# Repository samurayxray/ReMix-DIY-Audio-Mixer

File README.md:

# ReMix. DIY Audio Mixer

I want to build a desktop mixer for my PC using parts recovered from an old AMPRO mixer where possible.

## My idea

The planned design includes four faders, buttons, 6.35 mm audio jacks and a 3D-printed enclosure. I want mixer handle audio and control application volumes on my PC. These functions will need circuits and software.

## progress

I have opened old mixer removed a four‑channel board and photographed both sides. Board contains faders, rotary potentiometers, buttons, LEDs, XLR sockets and jack sockets. Two capacitors failed in mixer. I am keeping power supply out of this project. Recovered components have not been tested yet. I also have not confirmed fader resistance values or pin connections.

## Circuit and enclosure

I plan to use KiCad for schematic and PCB and AutoCAD for enclosure. Enclosure dimensions and mounting holes will depend on components actually used.

## Next steps

- Identify and test one fader.

- Check buttons and audio sockets.

- Decide how audio circuit and USB controls will work.

- Draw schematic and prepare parts list.

- Measure components before designing enclosure.

## Status

Project is still, in planning and component‑checking stage. No working prototype yet.

made by sx1

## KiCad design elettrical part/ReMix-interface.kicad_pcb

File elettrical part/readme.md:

I’m tired of writing README files for electronic circuit boards.

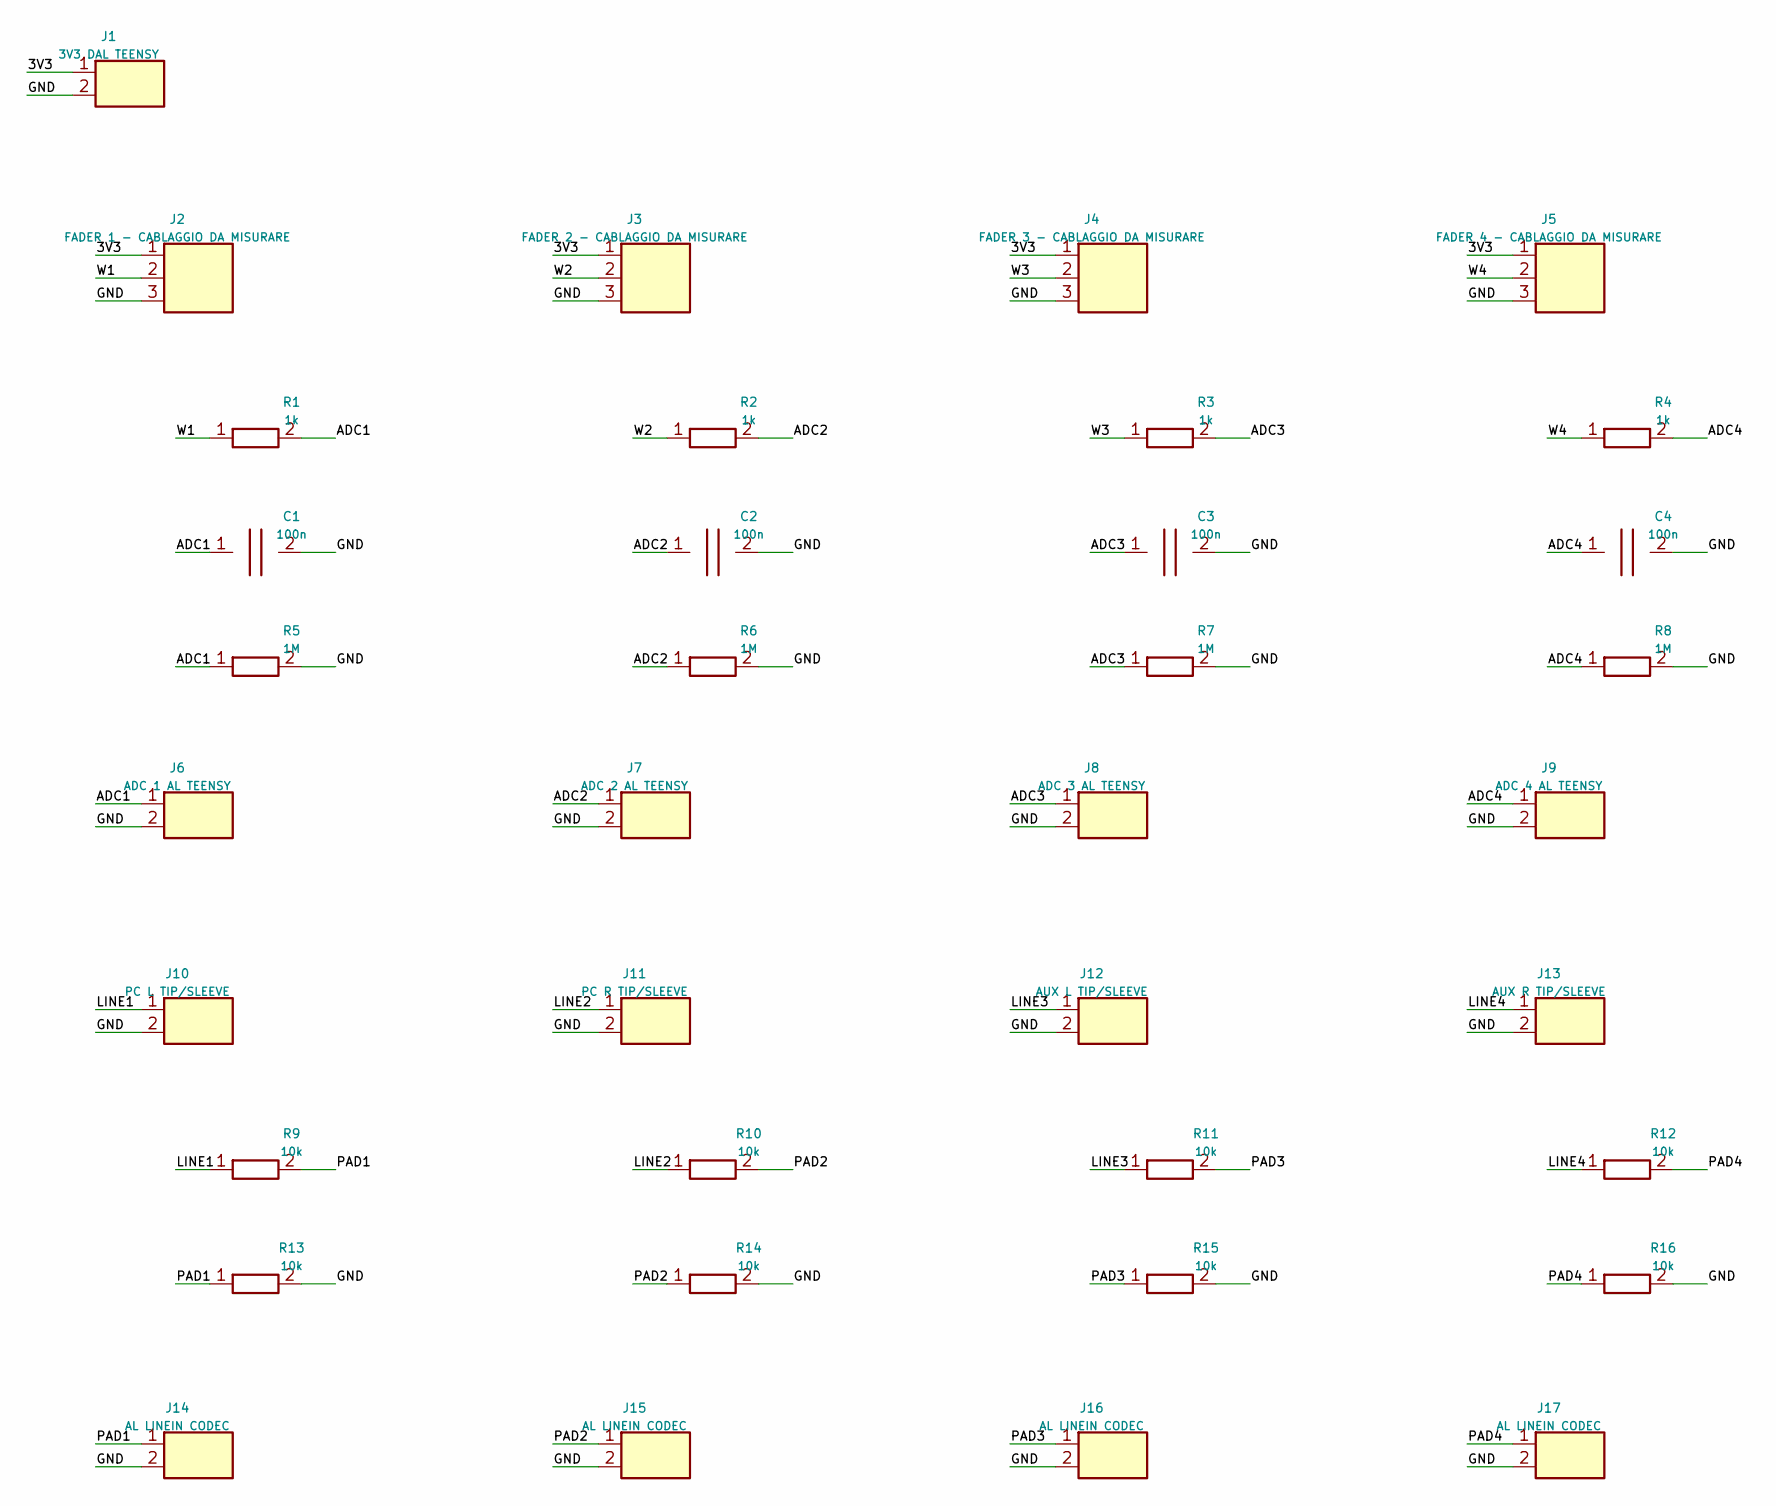
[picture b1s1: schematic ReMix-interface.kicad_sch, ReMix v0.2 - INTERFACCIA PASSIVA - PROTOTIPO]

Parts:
C1, C2, C3, C4: 100n; C_Radial_P2.50mm
J1: 3V3 DAL TEENSY; Port_1x02
J2: FADER 1 - CABLAGGIO DA MISURARE; Port_1x03
J3: FADER 2 - CABLAGGIO DA MISURARE; Port_1x03
J4: FADER 3 - CABLAGGIO DA MISURARE; Port_1x03
J5: FADER 4 - CABLAGGIO DA MISURARE; Port_1x03
J6: ADC 1 AL TEENSY; Port_1x02
J7: ADC 2 AL TEENSY; Port_1x02
J8: ADC 3 AL TEENSY; Port_1x02
J9: ADC 4 AL TEENSY; Port_1x02
J10: PC L TIP/SLEEVE; Port_1x02
J11: PC R TIP/SLEEVE; Port_1x02
J12: AUX L TIP/SLEEVE; Port_1x02
J13: AUX R TIP/SLEEVE; Port_1x02
J14, J15, J16, J17: AL LINEIN CODEC; Port_1x02
R1, R2, R3, R4: 1k; R_Axial_P7.62mm
R5, R6, R7, R8: 1M; R_Axial_P7.62mm
R9, R10, R11, R12, R13, R14, R15, R16: 10k; R_Axial_P7.62mm

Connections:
/3V3: J1.1, J2.1, J3.1, J4.1, J5.1
/ADC1: C1.1, J6.1, R1.2, R5.1
/ADC2: C2.1, J7.1, R2.2, R6.1
/ADC3: C3.1, J8.1, R3.2, R7.1
/ADC4: C4.1, J9.1, R4.2, R8.1
/GND: C1.2, C2.2, C3.2, C4.2, J1.2, J2.3, J3.3, J4.3, J5.3, J6.2, J7.2, J8.2, J9.2, J10.2, J11.2, J12.2, J13.2, J14.2, J15.2, J16.2, J17.2, R5.2, R6.2, R7.2, R8.2, R13.2, R14.2, R15.2, R16.2
/LINE1: J10.1, R9.1
/LINE2: J11.1, R10.1
/LINE3: J12.1, R11.1
/LINE4: J13.1, R12.1
/PAD1: J14.1, R9.2, R13.1
/PAD2: J15.1, R10.2, R14.1
/PAD3: J16.1, R11.2, R15.1
/PAD4: J17.1, R12.2, R16.1
/W1: J2.2, R1.1
/W2: J3.2, R2.1
/W3: J4.2, R3.1
/W4: J5.2, R4.1

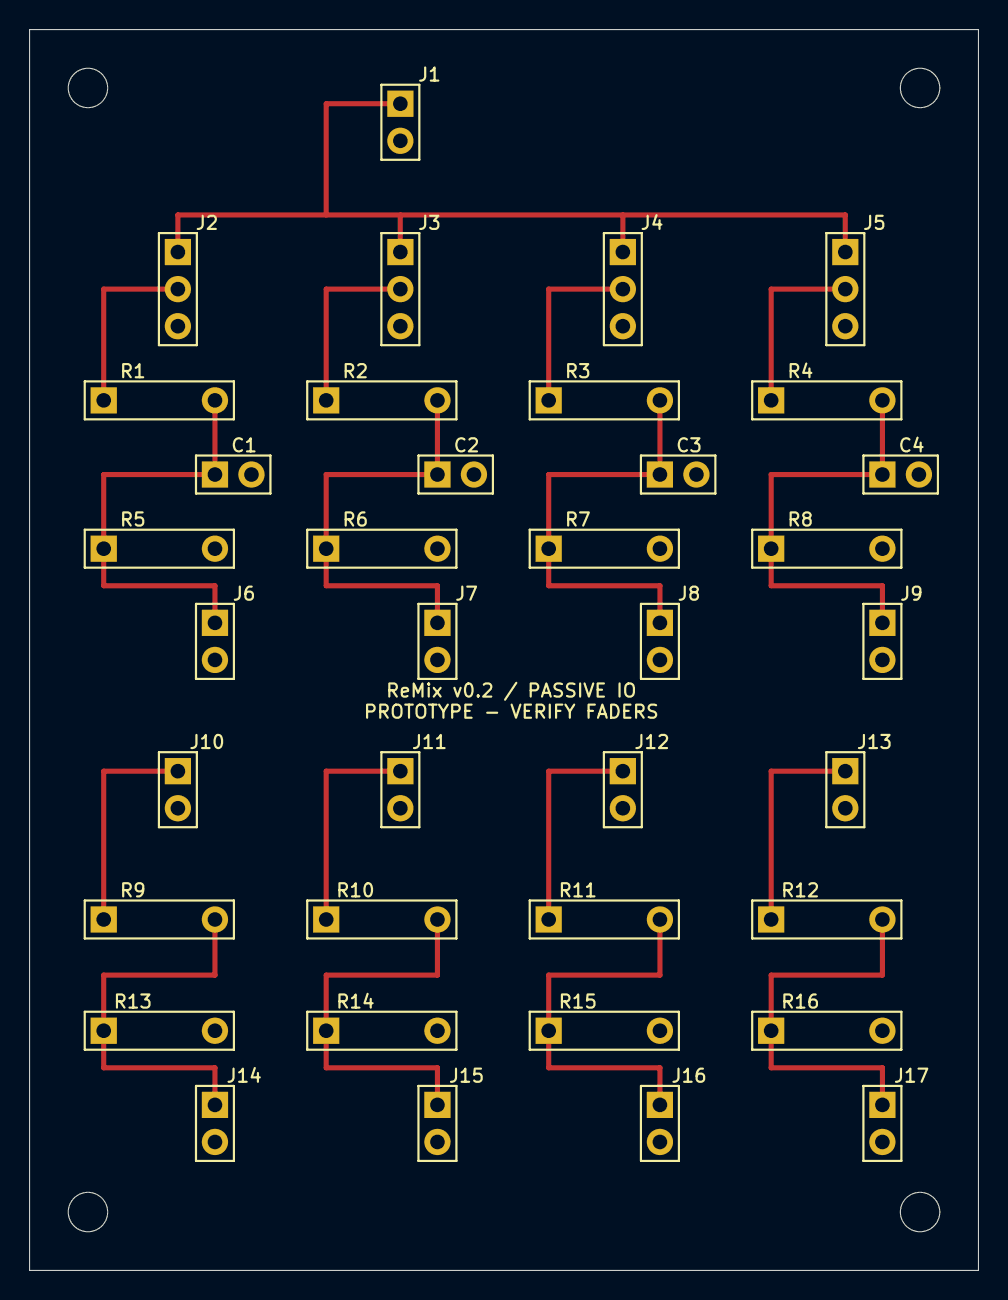
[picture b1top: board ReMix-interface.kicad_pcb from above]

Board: 2 copper layers, 65.0 x 85.0 mm, 41 parts (0 on the bottom side), 18 nets.

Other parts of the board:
H1, H2, H3, H4: M2.5 CLEARANCE
